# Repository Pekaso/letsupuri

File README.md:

# れつぷり!! letsupuri keyboard

48キー左右分離型キーボード「Let's Split」のリメイク版。

A remake of the 48 key split keyboard "Let's Split".
Left and right connection is using USB Type-C cable. And main and power circult are separated.

- 左右間をUSB-Cケーブルで接続
- PCBはメイン基板と電源基板で分離
- シリコン製ショックアブソーバーを使ったマウント

## ビルドガイド Build Guide

- ロープロファイル版ビルドガイド(日本語版): [Low Profile Ver. Build Guide (JP)](misc/buildguide/buildguide_lowprofile_jp.md)

れつぷり!!にはCherry MX版とLow Profile版があります。ハードウェアのメイン基板はCherry MX版（PCB_main_MX）とLow Profile版（PCB_main_lowprofile）で分かれています。電源基板（PCB_power）は共通です。

"れつぷり!!" has the Cherry MX version and the Low Profile version. The main board of the hardware is divided into the Cherry MX version (PCB_main_MX) and the Low Profile version (PCB_main_lowprofile). The power supply board (PCB_power) is the same for both versions.

> [!WARNING]
> Cherry MX版のハードウェア(PCB_main_MX)は現在のところ正しく動きません。The Cherry MX version (PCB_main_MX) does not currently work properly.

## ぴくちゃ

more detail at [pekaso.org](https://pekaso.org)

# License
This repository contains both hardware and firmware components, each under a different license.

- `hardware/`: Licensed under the MIT License
- `firmware/`: Licensed under the GPL License (inherited from the original repository)

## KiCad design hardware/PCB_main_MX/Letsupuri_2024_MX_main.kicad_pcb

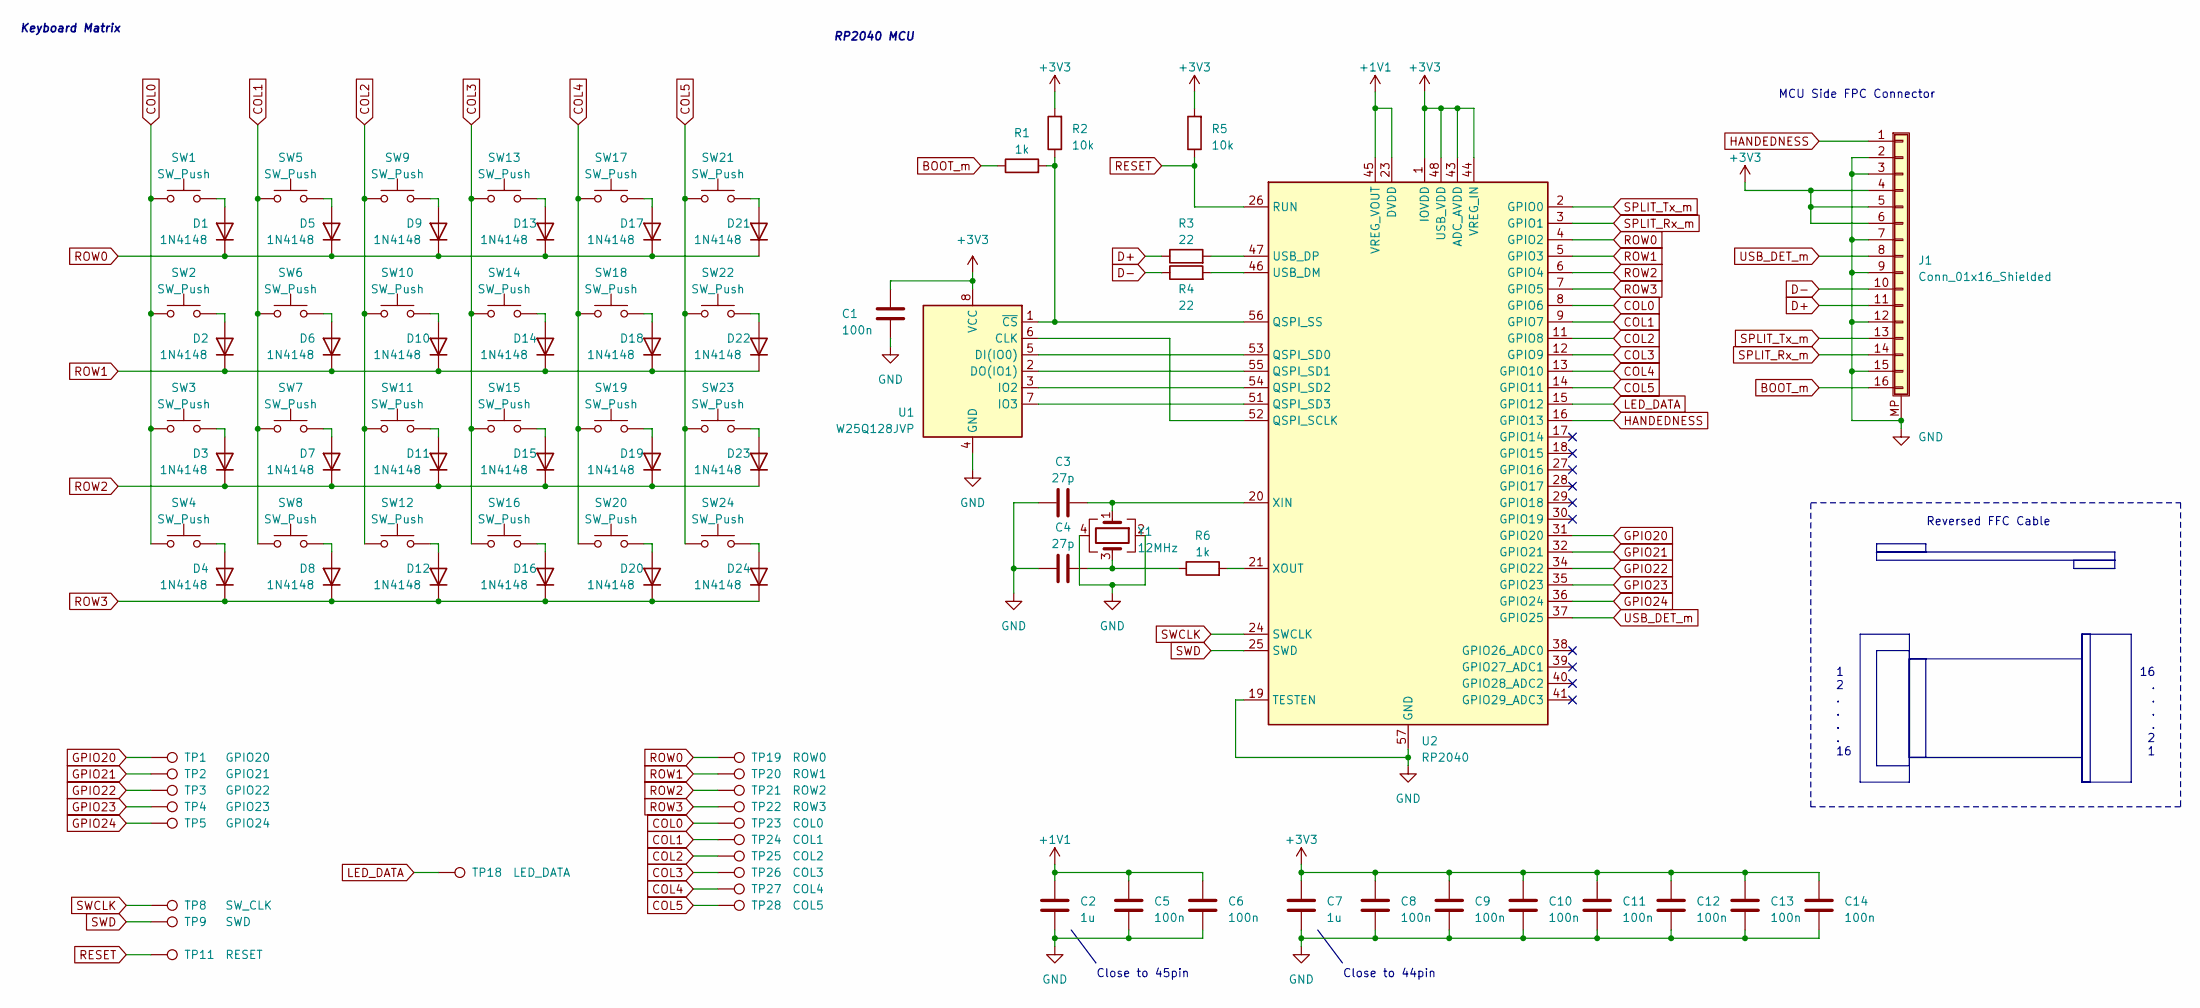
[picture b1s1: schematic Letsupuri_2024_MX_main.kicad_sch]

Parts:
C1, C5, C6, C8, C9, C10, C11, C12, C13, C14: 100n; C_0402_1005Metric; LCSC C1591
C2, C7: 1u; C_0402_1005Metric; LCSC C15849
C3, C4: 27p; C_0402_1005Metric; LCSC C107045
D1, D2, D3, D4, D5, D6, D7, D8, D9, D10, D11, D12, D13, D14, D15, D16, D17, D18, D19, D20, D21, D22, D23, D24: 1N4148; D_SOD-323; LCSC C81598
J1: Conn_01x16_Shielded; TE_1-1734839-6_1x16-1MP_P0.5mm_Horizontal
R1, R6: 1k; R_0402_1005Metric; LCSC C21190
R2, R5: 10k; R_0402_1005Metric; LCSC C25804
R3, R4: 22; R_0402_1005Metric; LCSC C23345
SW1, SW2, SW3, SW4, SW5, SW6, SW7, SW8, SW9, SW10, SW11, SW12, SW13, SW14, SW15, SW16, SW17, SW18, SW19, SW20, SW21, SW22, SW23, SW24: SW_Push; SW_Hotswap_Kailh_Choc_V1V2_1.00u
TP1: GPIO20; TestPoint_Pad_D1.0mm
TP2: GPIO21; TestPoint_Pad_D1.0mm
TP3: GPIO22; TestPoint_Pad_D1.0mm
TP4: GPIO23; TestPoint_Pad_D1.0mm
TP5: GPIO24; TestPoint_Pad_D1.0mm
TP8: SW_CLK; TestPoint_Pad_D1.0mm
TP9: SWD; TestPoint_Pad_D1.0mm
TP11: RESET; TestPoint_Pad_D1.0mm
TP18: LED_DATA; TestPoint_Pad_D1.0mm
TP19: ROW0; TestPoint_Pad_D1.0mm
TP20: ROW1; TestPoint_Pad_D1.0mm
TP21: ROW2; TestPoint_Pad_D1.0mm
TP22: ROW3; TestPoint_Pad_D1.0mm
TP23: COL0; TestPoint_Pad_D1.0mm
TP24: COL1; TestPoint_Pad_D1.0mm
TP25: COL2; TestPoint_Pad_D1.0mm
TP26: COL3; TestPoint_Pad_D1.0mm
TP27: COL4; TestPoint_Pad_D1.0mm
TP28: COL5; TestPoint_Pad_D1.0mm
U1: W25Q128JVP; Winbond_USON-8-1EP_3x2mm_P0.5mm_EP0.2x1.6mm; LCSC C190862
U2: RP2040; QFN-56-1EP_7x7mm_P0.4mm_EP3.2x3.2mm; LCSC C2040
Y1: 12MHz; Crystal_SMD_3225-4Pin_3.2x2.5mm; LCSC C9002

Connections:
+1V1: C2.2, C5.2, C6.2, U2.23 (DVDD), U2.45 (VREG_VOUT), U2.50 (DVDD); also elsewhere on the board
+3V3: C1.2, C7.2, C8.2, C9.2, C10.2, C11.2, C12.2, C13.2, C14.2, J1.4, J1.5, J1.6, R2.2, R5.2, U1.8 (VCC), U2.1 (IOVDD), U2.10 (IOVDD), U2.22 (IOVDD), U2.33 (IOVDD), U2.42 (IOVDD), U2.43 (ADC_AVDD), U2.44 (VREG_IN), U2.48 (USB_VDD), U2.49 (IOVDD)
BOOT_m: J1.16, R1.1
COL0: SW1.1, SW2.1, SW3.1, SW4.1, TP23.1, U2.8 (GPIO6)
COL1: SW5.1, SW6.1, SW7.1, SW8.1, TP24.1, U2.9 (GPIO7)
COL2: SW9.1, SW10.1, SW11.1, SW12.1, TP25.1, U2.11 (GPIO8)
COL3: SW13.1, SW14.1, SW15.1, SW16.1, TP26.1, U2.12 (GPIO9)
COL4: SW17.1, SW18.1, SW19.1, SW20.1, TP27.1, U2.13 (GPIO10)
COL5: SW21.1, SW22.1, SW23.1, SW24.1, TP28.1, U2.14 (GPIO11)
D+: J1.11, R3.1
D-: J1.10, R4.1
GND: C1.1, C2.1, C3.1, C4.1, C5.1, C6.1, C7.1, C8.1, C9.1, C10.1, C11.1, C12.1, C13.1, C14.1, J1.2, J1.3, J1.7, J1.9, J1.12, J1.15, J1.MP (Shield), U1.4 (GND), U2.19 (TESTEN), U2.57 (GND), Y1.2, Y1.4
GPIO20: TP1.1, U2.31 (GPIO20)
GPIO21: TP2.1, U2.32 (GPIO21)
GPIO22: TP3.1, U2.34 (GPIO22)
GPIO23: TP4.1, U2.35 (GPIO23)
GPIO24: TP5.1, U2.36 (GPIO24)
HANDEDNESS: J1.1, U2.16 (GPIO13)
LED_DATA: TP18.1, U2.15 (GPIO12)
unnamed: C4.2, R6.1, Y1.3
unnamed: D1.2 (A), SW1.2
unnamed: D2.2 (A), SW2.2
unnamed: D3.2 (A), SW3.2
unnamed: D4.2 (A), SW4.2
unnamed: D5.2 (A), SW5.2
unnamed: D6.2 (A), SW6.2
unnamed: D7.2 (A), SW7.2
unnamed: D8.2 (A), SW8.2
unnamed: D9.2 (A), SW9.2
unnamed: D10.2 (A), SW10.2
unnamed: D11.2 (A), SW11.2
unnamed: D12.2 (A), SW12.2
unnamed: D13.2 (A), SW13.2
unnamed: D14.2 (A), SW14.2
unnamed: D15.2 (A), SW15.2
unnamed: D16.2 (A), SW16.2
unnamed: D17.2 (A), SW17.2
unnamed: D18.2 (A), SW18.2
unnamed: D19.2 (A), SW19.2
unnamed: D20.2 (A), SW20.2
unnamed: D21.2 (A), SW21.2
unnamed: D22.2 (A), SW22.2
unnamed: D23.2 (A), SW23.2
unnamed: D24.2 (A), SW24.2
unnamed: U1.6 (CLK), U2.52 (QSPI_SCLK)
unnamed: U1.5 (DI(IO0)), U2.53 (QSPI_SD0)
unnamed: U1.2 (DO(IO1)), U2.55 (QSPI_SD1)
unnamed: U1.3 (IO2), U2.54 (QSPI_SD2)
unnamed: U1.7 (IO3), U2.51 (QSPI_SD3)
unnamed: R1.2, R2.1, U1.1 (~CS), U2.56 (QSPI_SS)
unnamed: R4.2, U2.46 (USB_DM)
unnamed: R3.2, U2.47 (USB_DP)
unnamed: C3.2, U2.20 (XIN), Y1.1
unnamed: R6.2, U2.21 (XOUT)
RESET: R5.1, TP11.1, U2.26 (RUN)
ROW0: D1.1 (K), D5.1 (K), D9.1 (K), D13.1 (K), D17.1 (K), D21.1 (K), TP19.1, U2.4 (GPIO2)
ROW1: D2.1 (K), D6.1 (K), D10.1 (K), D14.1 (K), D18.1 (K), D22.1 (K), TP20.1, U2.5 (GPIO3)
ROW2: D3.1 (K), D7.1 (K), D11.1 (K), D15.1 (K), D19.1 (K), D23.1 (K), TP21.1, U2.6 (GPIO4)
ROW3: D4.1 (K), D8.1 (K), D12.1 (K), D16.1 (K), D20.1 (K), D24.1 (K), TP22.1, U2.7 (GPIO5)
SPLIT_Rx_m: J1.14, U2.3 (GPIO1)
SPLIT_Tx_m: J1.13, U2.2 (GPIO0)
SWCLK: TP8.1, U2.24 (SWCLK)
SWD: TP9.1, U2.25 (SWD)
USB_DET_m: J1.8, U2.37 (GPIO25)

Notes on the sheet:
1 2 . . . . 16
RP2040 MCU
Close to 44pin
Keyboard Matrix
MCU Side FPC Connector
Reversed FFC Cable
Close to 45pin
16 . . . . 2 1

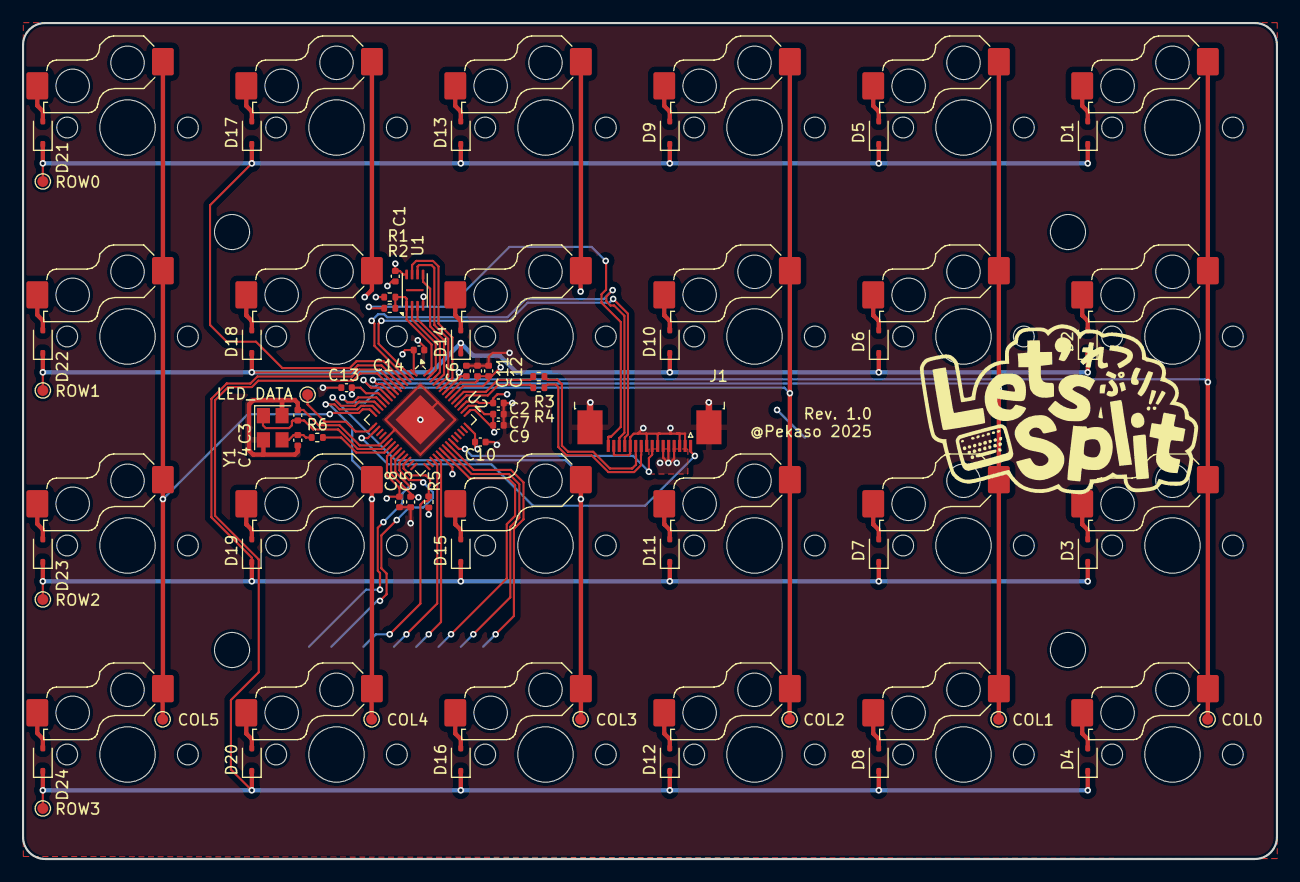
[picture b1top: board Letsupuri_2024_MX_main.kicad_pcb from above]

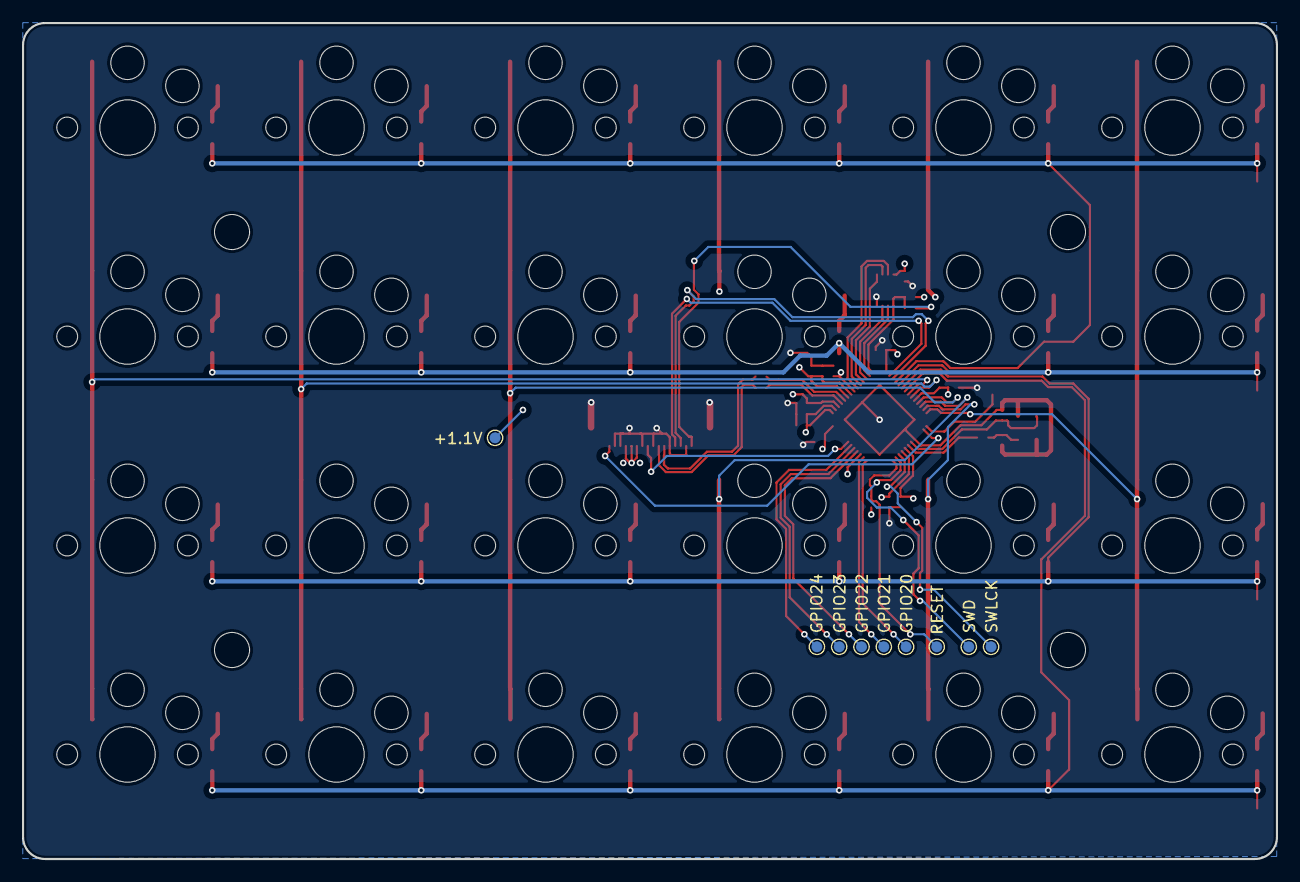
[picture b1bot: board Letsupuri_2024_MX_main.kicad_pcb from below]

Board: 4 copper layers, 114.3 x 76.2 mm, 92 parts (33 on the bottom side), 64 nets.

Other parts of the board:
TP16: +1.1V_L; TestPoint_Pad_D1.0mm

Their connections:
+1V1: TP16.1; also elsewhere on the board

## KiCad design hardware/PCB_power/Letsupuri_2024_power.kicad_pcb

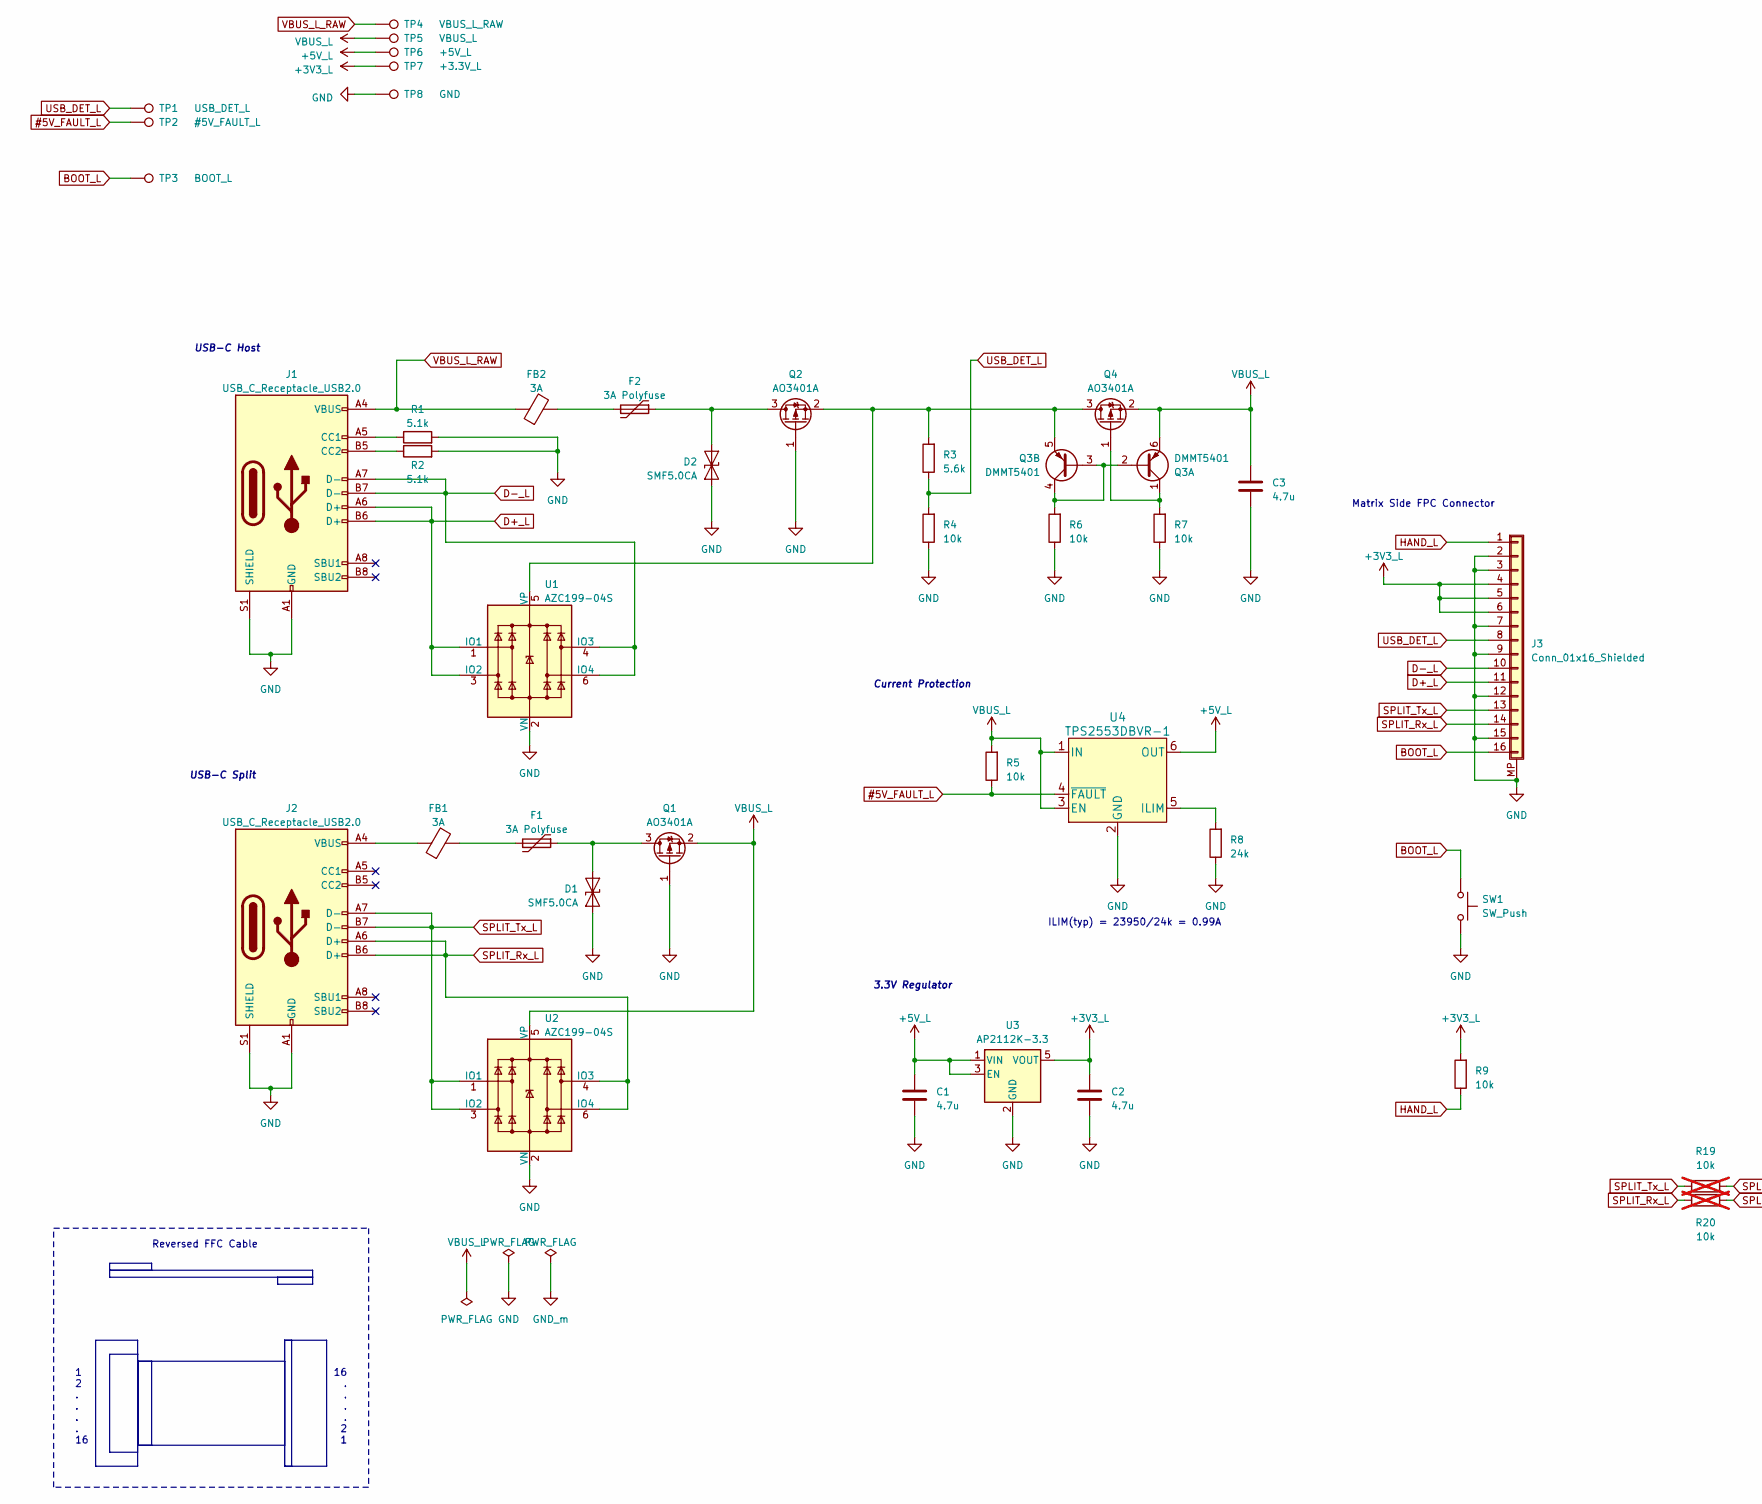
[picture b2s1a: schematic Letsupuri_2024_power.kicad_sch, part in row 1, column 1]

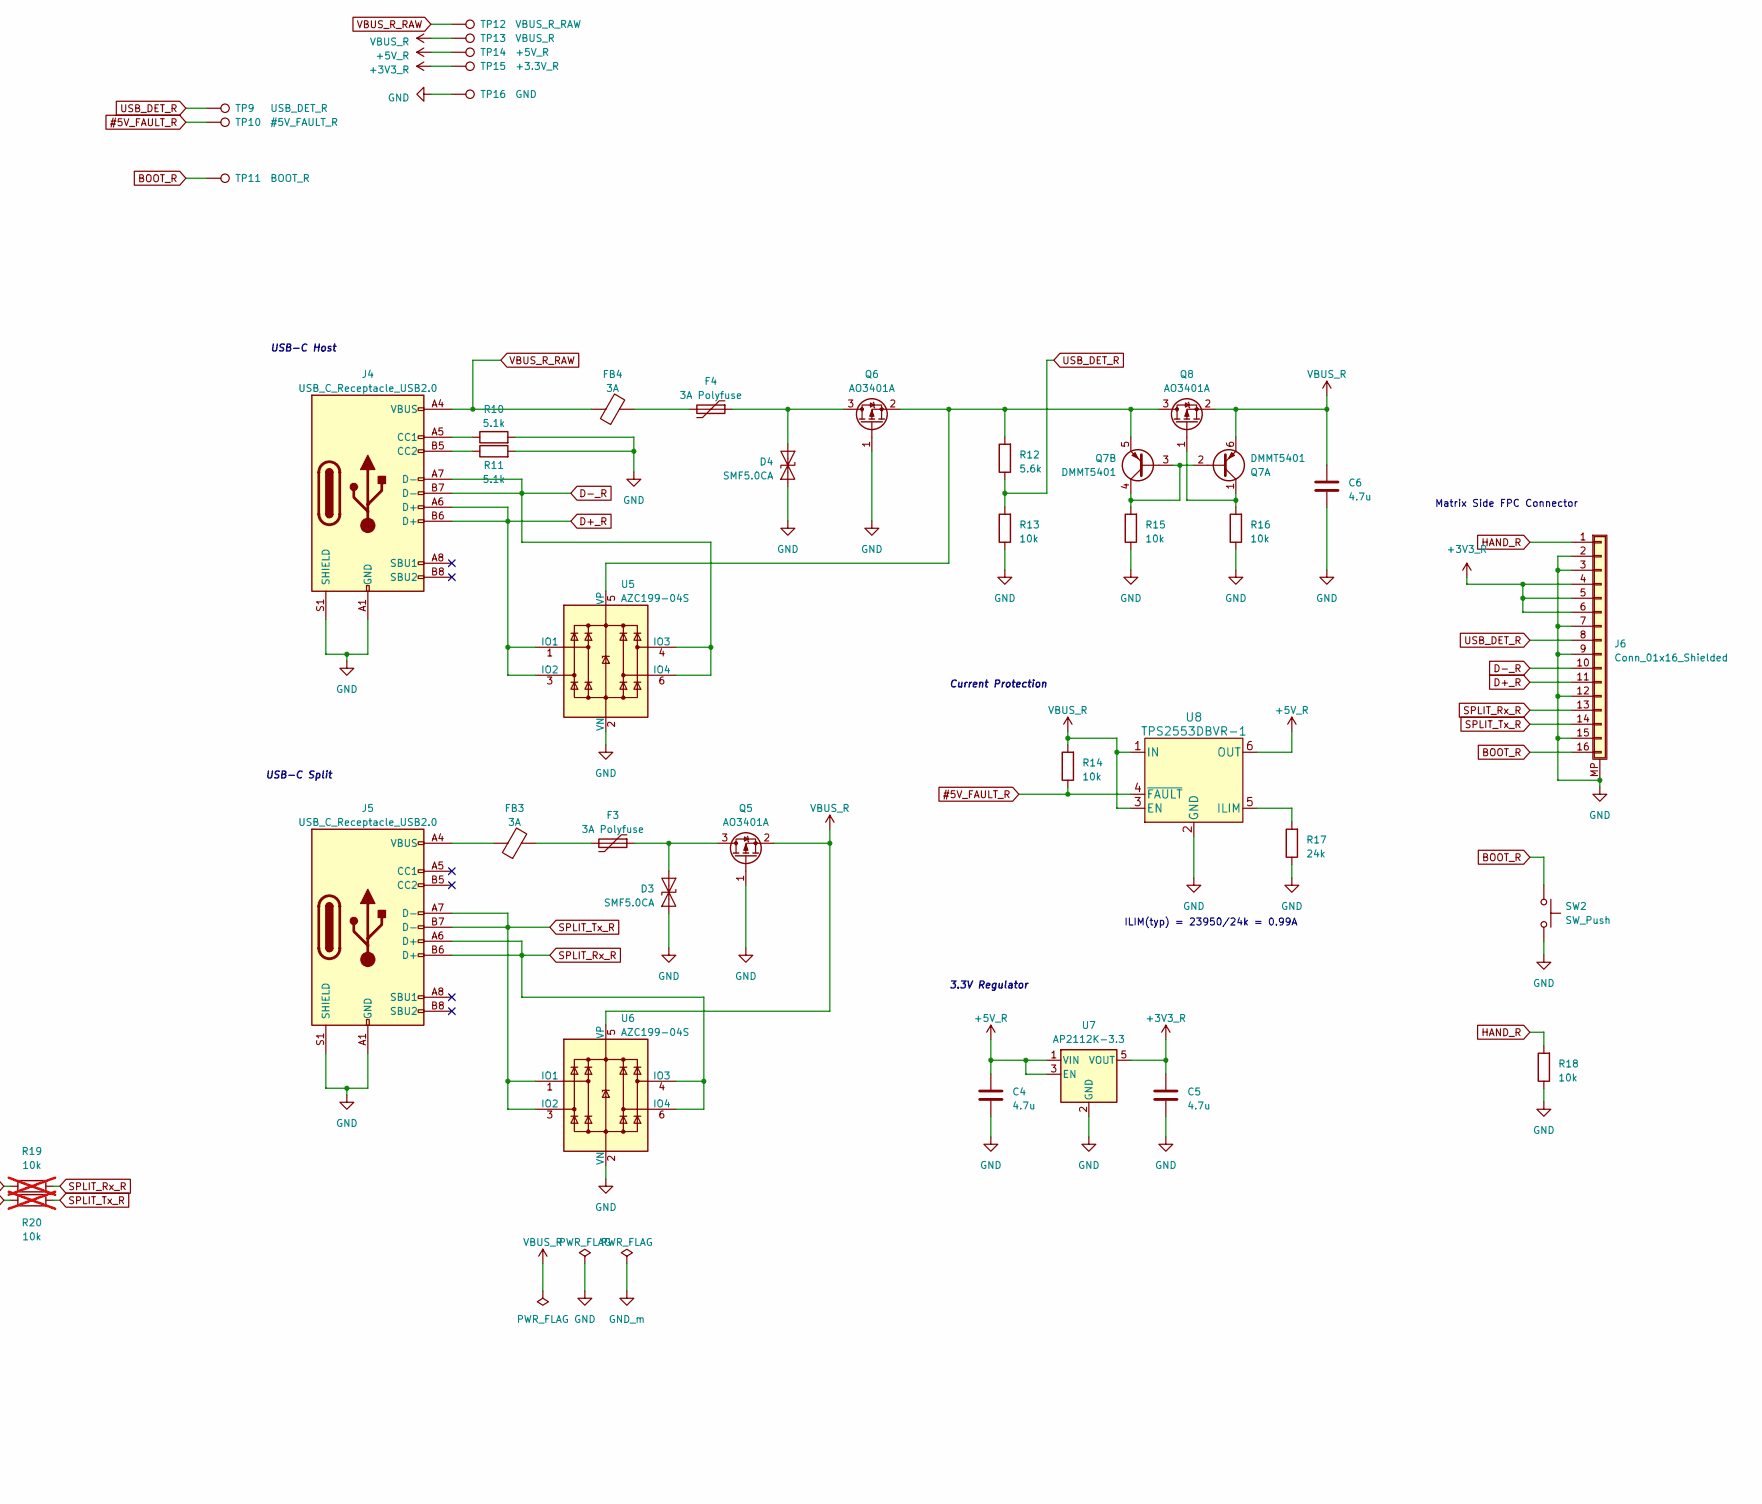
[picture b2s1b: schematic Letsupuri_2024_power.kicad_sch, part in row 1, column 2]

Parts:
C1, C2, C3, C4, C5, C6: 4.7u; C_0603_1608Metric; LCSC C19666
D1, D2, D3, D4: SMF5.0CA; D_SOD-123; LCSC C908214
F1, F2, F3, F4: 3A Polyfuse; C_1206_3216Metric; LCSC C3020147
FB1, FB2, FB3, FB4: 3A; C_0805_2012Metric; LCSC C142054
J1, J2, J4, J5: USB_C_Receptacle_USB2.0; USB_C_Receptacle_HRO_TYPE-C-31-M-12
J3, J6: Conn_01x16_Shielded; TE_1-1734839-6_1x16-1MP_P0.5mm_Horizontal
Q1, Q2, Q4, Q5, Q6, Q8: AO3401A; SOT-23; LCSC C15127
Q3, Q7: DMMT5401; SOT-23-6; LCSC C154733
R1, R2, R10, R11: 5.1k; R_0603_1608Metric; LCSC C23186
R3, R12: 5.6k; R_0603_1608Metric; LCSC C23189
R4, R5, R6, R7, R9, R13, R14, R15, R16, R18: 10k; R_0603_1608Metric; LCSC C25804
R8, R17: 24k; R_0603_1608Metric; LCSC C23352
R19, R20: 10k; R_0603_1608Metric; LCSC C25804; not fitted
SW1, SW2: SW_Push; TS-1088-AR02016; LCSC C720477
TP1: USB_DET_L; TestPoint_Pad_D1.0mm
TP2: #5V_FAULT_L; TestPoint_Pad_D1.0mm
TP3: BOOT_L; TestPoint_Pad_D1.0mm
TP4: VBUS_L_RAW; TestPoint_Pad_D1.0mm
TP5: VBUS_L; TestPoint_Pad_D1.0mm
TP6: +5V_L; TestPoint_Pad_D1.0mm
TP7: +3.3V_L; TestPoint_Pad_D1.0mm
TP8, TP16: GND; TestPoint_Pad_D1.0mm
TP9: USB_DET_R; TestPoint_Pad_D1.0mm
TP10: #5V_FAULT_R; TestPoint_Pad_D1.0mm
TP11: BOOT_R; TestPoint_Pad_D1.0mm
TP12: VBUS_R_RAW; TestPoint_Pad_D1.0mm
TP13: VBUS_R; TestPoint_Pad_D1.0mm
TP14: +5V_R; TestPoint_Pad_D1.0mm
TP15: +3.3V_R; TestPoint_Pad_D1.0mm
U1, U2, U5, U6: AZC199-04S; SOT-23-6; LCSC C2901321
U3, U7: AP2112K-3.3; SOT-23-5; LCSC C3021085
U4, U8: TPS2553DBVR-1; SOT-23-6; LCSC C111738

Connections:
#5V_FAULT_L: R5.1, TP2.1, U4.4 (~FAULT)
#5V_FAULT_R: R14.1, TP10.1, U8.4 (~FAULT)
+3V3_L: C2.2, J3.4, J3.5, J3.6, R9.2, TP7.1, U3.5 (VOUT)
+3V3_R: C5.2, J6.4, J6.5, J6.6, TP15.1, U7.5 (VOUT)
+5V_L: C1.2, TP6.1, U3.1 (VIN), U3.3 (EN), U4.6 (OUT)
+5V_R: C4.2, TP14.1, U7.1 (VIN), U7.3 (EN), U8.6 (OUT)
BOOT_L: J3.16, SW1.1, TP3.1
BOOT_R: J6.16, SW2.1, TP11.1
D+_L: J1.A6 (D+), J1.B6 (D+), J3.11, U1.1 (IO1), U1.3 (IO2)
D+_R: J4.A6 (D+), J4.B6 (D+), J6.11, U5.1 (IO1), U5.3 (IO2)
D-_L: J1.A7 (D-), J1.B7 (D-), J3.10, U1.4 (IO3), U1.6 (IO4)
D-_R: J4.A7 (D-), J4.B7 (D-), J6.10, U5.4 (IO3), U5.6 (IO4)
GND: C1.1, C2.1, C3.1, C4.1, C5.1, C6.1, D1.1 (A1), D2.1 (A1), D3.1 (A1), D4.1 (A1), J1.A1 (GND), J1.A12 (GND), J1.B1 (GND), J1.B12 (GND), J1.S1 (SHIELD), J2.A1 (GND), J2.A12 (GND), J2.B1 (GND), J2.B12 (GND), J2.S1 (SHIELD), J3.2, J3.3, J3.7, J3.9, J3.12, J3.15, J3.MP (Shield), J4.A1 (GND), J4.A12 (GND), J4.B1 (GND), J4.B12 (GND), J4.S1 (SHIELD), J5.A1 (GND), J5.A12 (GND), J5.B1 (GND), J5.B12 (GND), J5.S1 (SHIELD), J6.2, J6.3, J6.7, J6.9, J6.12, J6.15, J6.MP (Shield), Q1.1 (G), Q2.1 (G), Q5.1 (G), Q6.1 (G), R1.2, R2.2, R4.1, R6.1, R7.1, R8.1, R10.2, R11.2, R13.1, R15.1, R16.1, R17.1, R18.1, SW1.2, SW2.2, TP8.1, TP16.1, U1.2 (VN), U2.2 (VN), U3.2 (GND), U4.2 (GND), U5.2 (VN), U6.2 (VN), U7.2 (GND), U8.2 (GND)
HAND_L: J3.1, R9.1
HAND_R: J6.1, R18.2
unnamed: D1.2 (A2), F1.1, Q1.3 (D)
unnamed: D2.2 (A2), F2.1, Q2.3 (D)
unnamed: D3.2 (A2), F3.1, Q5.3 (D)
unnamed: D4.2 (A2), F4.1, Q6.3 (D)
unnamed: F1.2, FB1.2
unnamed: F2.2, FB2.2
unnamed: F3.2, FB3.2
unnamed: F4.2, FB4.2
unnamed: FB1.1, J2.A4 (VBUS), J2.A9 (VBUS), J2.B4 (VBUS), J2.B9 (VBUS)
unnamed: FB3.1, J5.A4 (VBUS), J5.A9 (VBUS), J5.B4 (VBUS), J5.B9 (VBUS)
unnamed: J1.A5 (CC1), R1.1
unnamed: J1.B5 (CC2), R2.1
unnamed: J4.A5 (CC1), R10.1
unnamed: J4.B5 (CC2), R11.1
unnamed: Q2.2 (S), Q3.5 (E2), Q4.3 (D), R3.2, U1.5 (VP)
unnamed: Q3.2 (B1), Q3.3 (B2), Q3.4 (C2), R6.2
unnamed: Q3.1 (C1), Q4.1 (G), R7.2
unnamed: Q6.2 (S), Q7.5 (E2), Q8.3 (D), R12.2, U5.5 (VP)
unnamed: Q7.2 (B1), Q7.3 (B2), Q7.4 (C2), R15.2
unnamed: Q7.1 (C1), Q8.1 (G), R16.2
unnamed: R8.2, U4.5 (ILIM)
unnamed: R17.2, U8.5 (ILIM)
SPLIT_Rx_L: J2.A6 (D+), J2.B6 (D+), J3.14, R20.2, U2.4 (IO3), U2.6 (IO4)
SPLIT_Rx_R: J5.A6 (D+), J5.B6 (D+), J6.13, R19.1, U6.4 (IO3), U6.6 (IO4)
SPLIT_Tx_L: J2.A7 (D-), J2.B7 (D-), J3.13, R19.2, U2.1 (IO1), U2.3 (IO2)
SPLIT_Tx_R: J5.A7 (D-), J5.B7 (D-), J6.14, R20.1, U6.1 (IO1), U6.3 (IO2)
USB_DET_L: J3.8, R3.1, R4.2, TP1.1
USB_DET_R: J6.8, R12.1, R13.2, TP9.1
VBUS_L: C3.2, Q1.2 (S), Q3.6 (E1), Q4.2 (S), R5.2, TP5.1, U2.5 (VP), U4.1 (IN), U4.3 (EN)
VBUS_L_RAW: FB2.1, J1.A4 (VBUS), J1.A9 (VBUS), J1.B4 (VBUS), J1.B9 (VBUS), TP4.1
VBUS_R: C6.2, Q5.2 (S), Q7.6 (E1), Q8.2 (S), R14.2, TP13.1, U6.5 (VP), U8.1 (IN), U8.3 (EN)
VBUS_R_RAW: FB4.1, J4.A4 (VBUS), J4.A9 (VBUS), J4.B4 (VBUS), J4.B9 (VBUS), TP12.1

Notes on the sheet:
3.3V Regulator
1 2 . . . . 16
USB-C Split
ILIM(typ) = 23950/24k = 0.99A
USB-C Host
Current Protection
Matrix Side FPC Connector
Reversed FFC Cable
16 . . . . 2 1

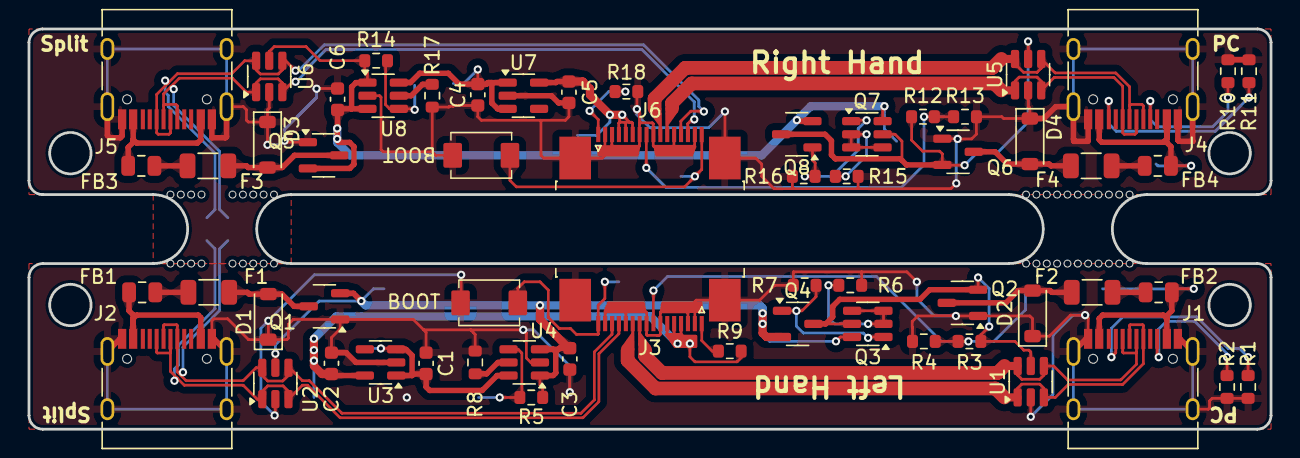
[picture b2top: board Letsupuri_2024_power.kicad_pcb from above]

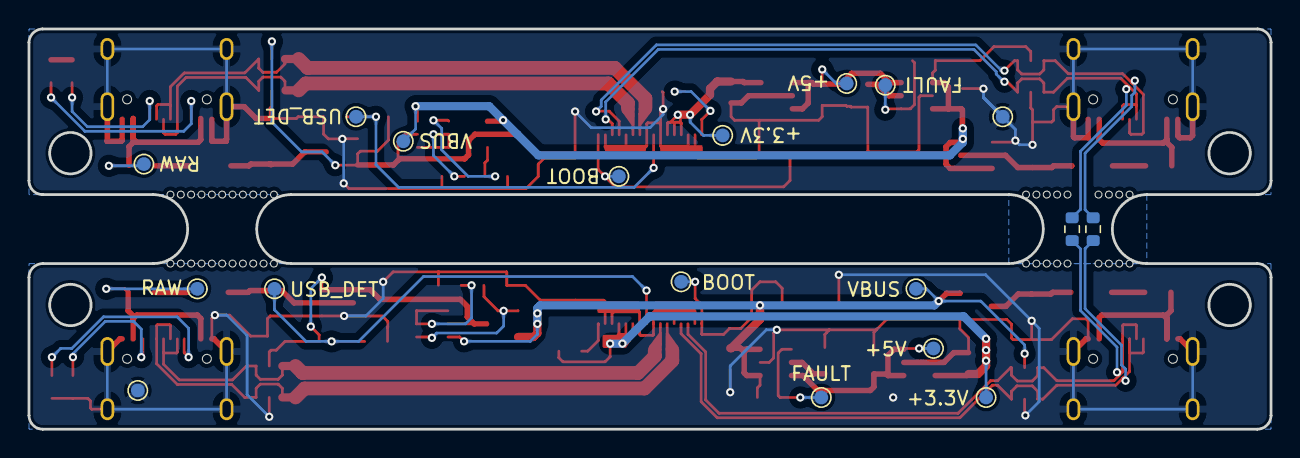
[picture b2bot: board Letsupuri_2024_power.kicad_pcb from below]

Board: 2 copper layers, 90.0 x 29.0 mm, 80 parts (18 on the bottom side), 47 nets.

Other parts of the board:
mouse-bite-2mm-slot, mouse-bite-2mm-slot#2: VAL**; mouse-bite-5mm-slot

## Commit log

2025-03-15 fix path
2025-03-15 Create LICENSE-MIT
2025-03-15 Create LICENSE-GPL
2025-03-21 add buildguide
2025-03-22 update buildguide + tri-mode fix firmware
